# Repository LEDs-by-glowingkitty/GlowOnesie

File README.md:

# GlowOnesie
All design files and details about the cat onesies which I wear, with glowing moving ears. Great for everyday use, parties and other occasions.

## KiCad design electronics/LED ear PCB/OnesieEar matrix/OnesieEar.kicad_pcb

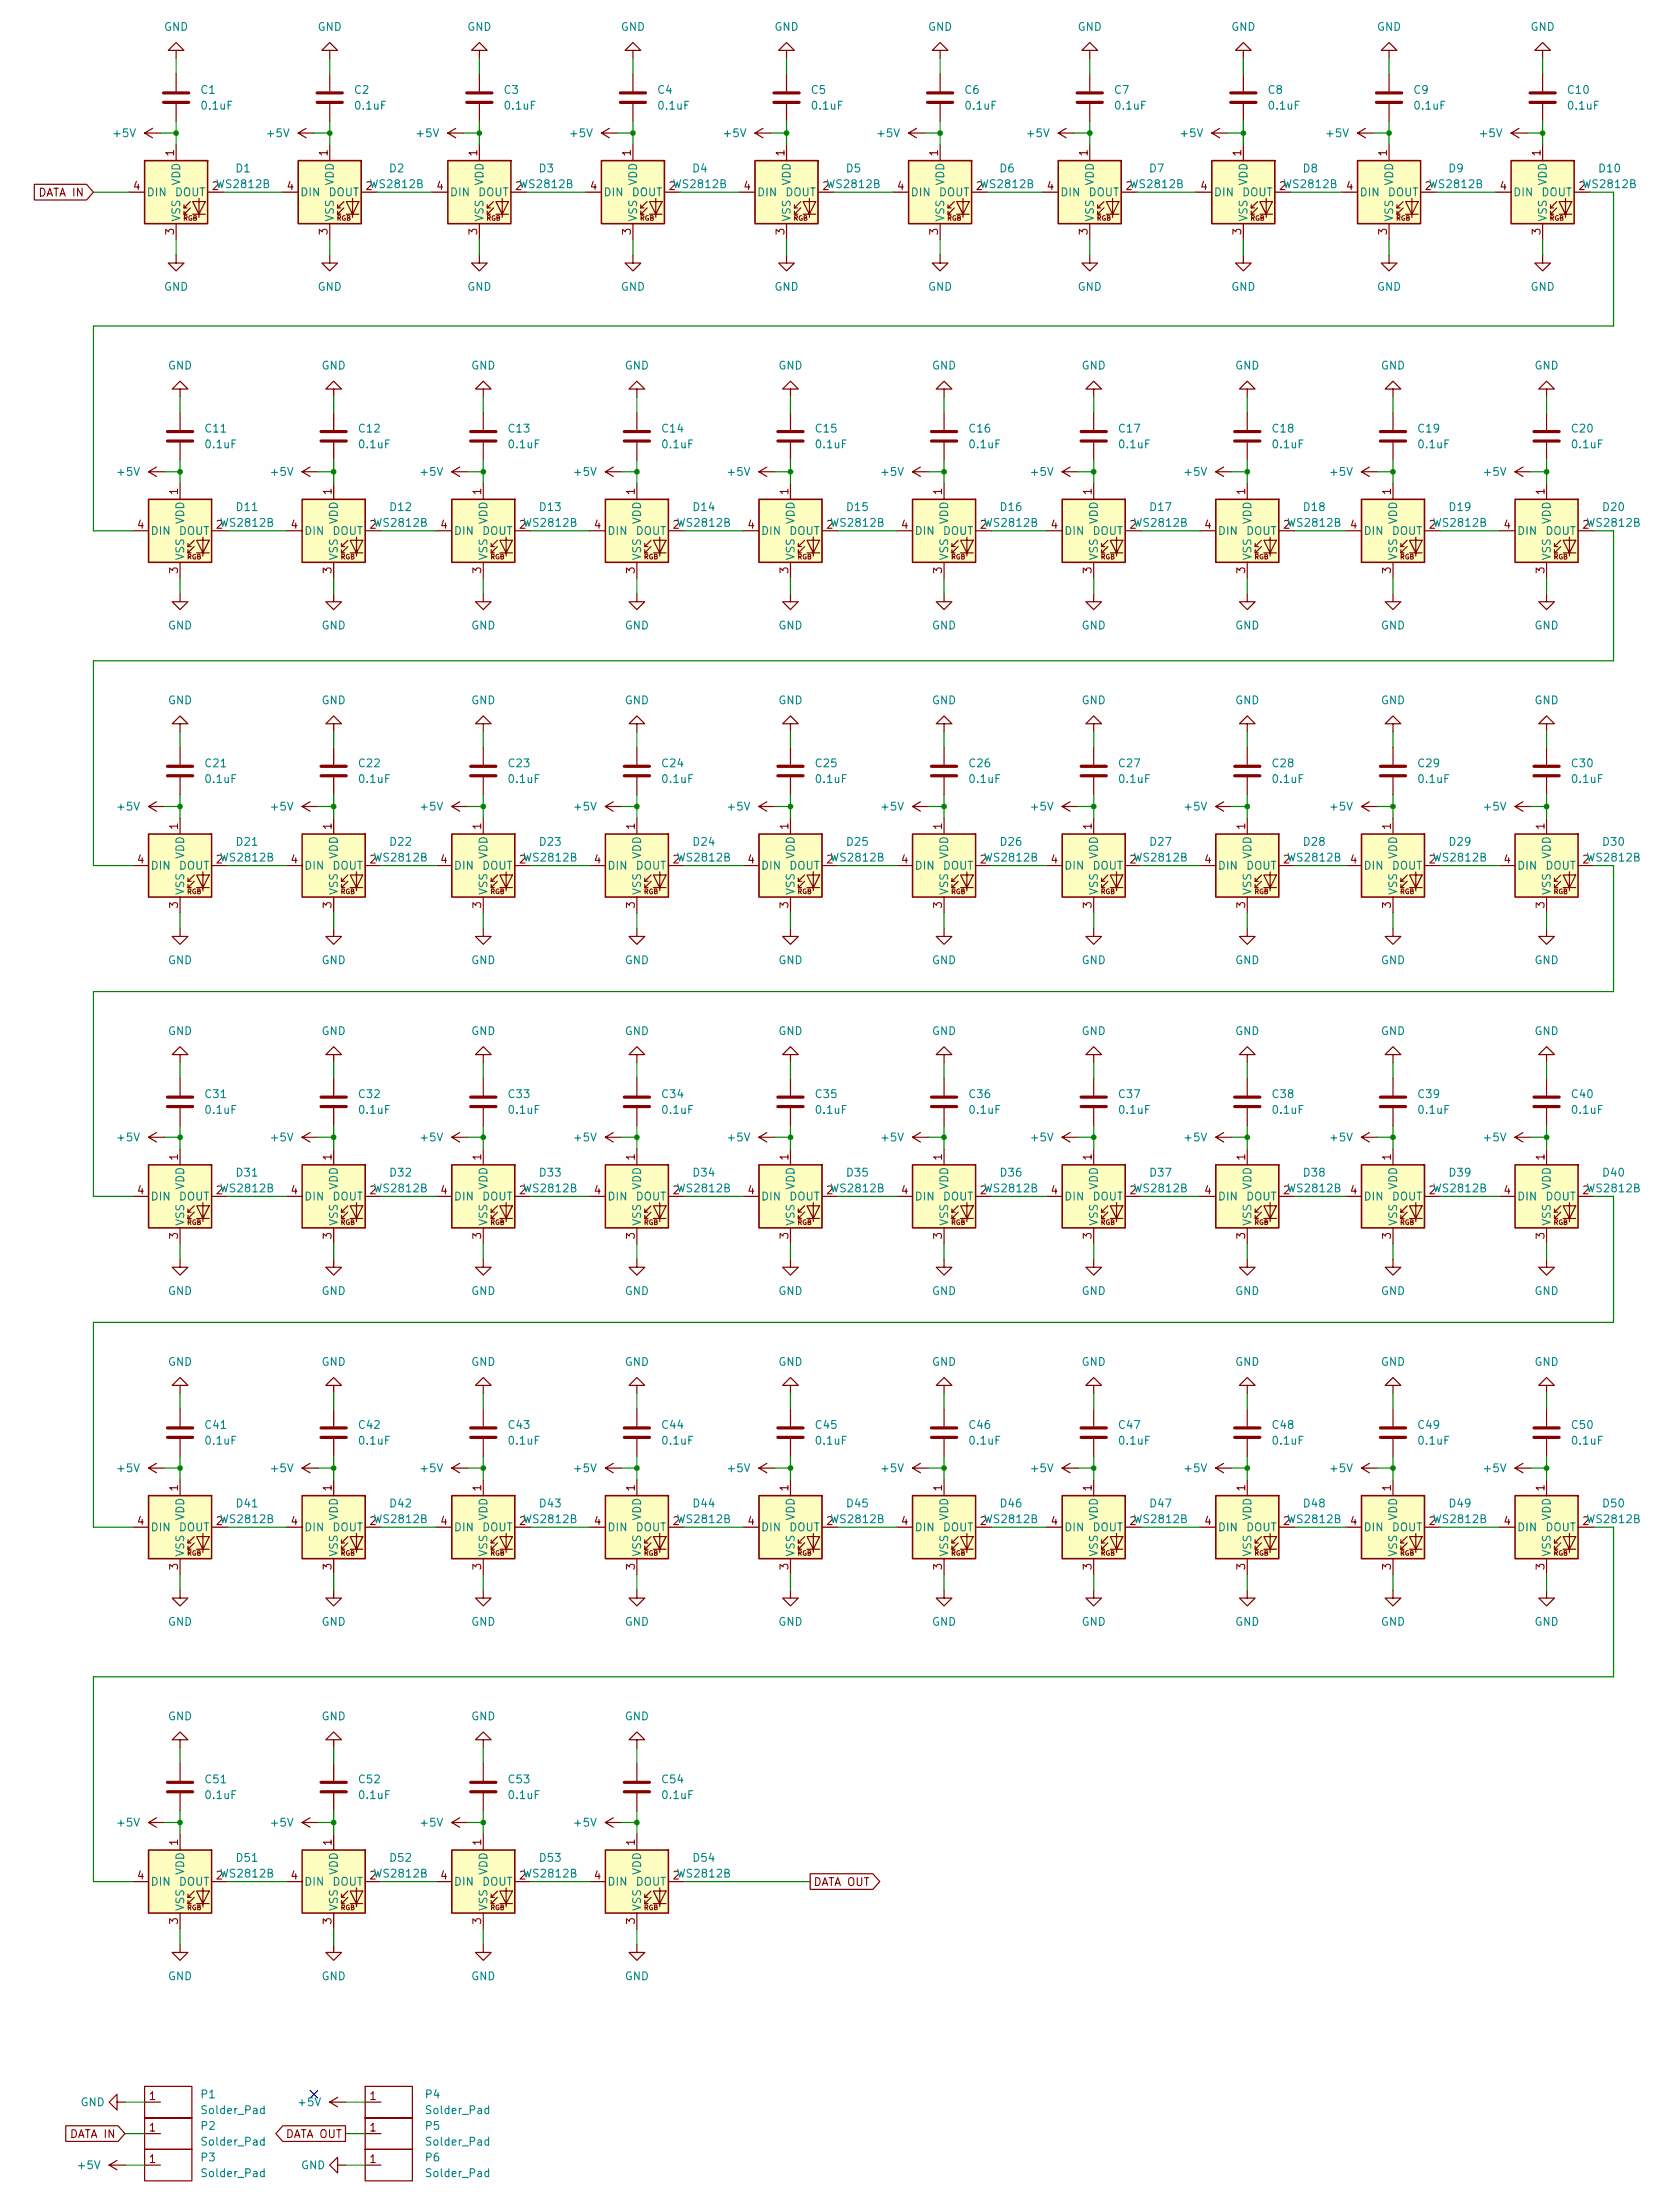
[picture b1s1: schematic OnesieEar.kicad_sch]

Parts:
C1, C2, C3, C4, C5, C6, C7, C8, C9, C10, C11, C12, C13, C14, C15, C16, C17, C18, C19, C20, C21, C22, C23, C24, C25, C26, C27, C28, C29, C30, C31, C32, C33, C34, C35, C36, C37, C38, C39, C40, C41, C42, C43, C44, C45, C46, C47, C48, C49, C50, C51, C52, C53, C54: 0.1uF; C_0603_1608Metric_Pad1.08x0.95mm_HandSolder; LCSC # C14663
D1, D2, D3, D4, D5, D6, D7, D8, D9, D10, D11, D12, D13, D14, D15, D16, D17, D18, D19, D20, D21, D22, D23, D24, D25, D26, D27, D28, D29, D30, D31, D32, D33, D34, D35, D36, D37, D38, D39, D40, D41, D42, D43, D44, D45, D46, D47, D48, D49, D50, D51, D52, D53, D54: WS2812B; LED_WS2812B_PLCC4_5.0x5.0mm_P3.2mm; LCSC # C2843785
P1, P2, P3, P4, P5, P6: Solder_Pad; Solder pad

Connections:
+5V: C1.1, C2.1, C3.1, C4.1, C5.1, C6.1, C7.1, C8.1, C9.1, C10.1, C11.1, C12.1, C13.1, C14.1, C15.1, C16.1, C17.1, C18.1, C19.1, C20.1, C21.1, C22.1, C23.1, C24.1, C25.1, C26.1, C27.1, C28.1, C29.1, C30.1, C31.1, C32.1, C33.1, C34.1, C35.1, C36.1, C37.1, C38.1, C39.1, C40.1, C41.1, C42.1, C43.1, C44.1, C45.1, C46.1, C47.1, C48.1, C49.1, C50.1, C51.1, C52.1, C53.1, C54.1, D1.1 (VDD), D2.1 (VDD), D3.1 (VDD), D4.1 (VDD), D5.1 (VDD), D6.1 (VDD), D7.1 (VDD), D8.1 (VDD), D9.1 (VDD), D10.1 (VDD), D11.1 (VDD), D12.1 (VDD), D13.1 (VDD), D14.1 (VDD), D15.1 (VDD), D16.1 (VDD), D17.1 (VDD), D18.1 (VDD), D19.1 (VDD), D20.1 (VDD), D21.1 (VDD), D22.1 (VDD), D23.1 (VDD), D24.1 (VDD), D25.1 (VDD), D26.1 (VDD), D27.1 (VDD), D28.1 (VDD), D29.1 (VDD), D30.1 (VDD), D31.1 (VDD), D32.1 (VDD), D33.1 (VDD), D34.1 (VDD), D35.1 (VDD), D36.1 (VDD), D37.1 (VDD), D38.1 (VDD), D39.1 (VDD), D40.1 (VDD), D41.1 (VDD), D42.1 (VDD), D43.1 (VDD), D44.1 (VDD), D45.1 (VDD), D46.1 (VDD), D47.1 (VDD), D48.1 (VDD), D49.1 (VDD), D50.1 (VDD), D51.1 (VDD), D52.1 (VDD), D53.1 (VDD), D54.1 (VDD), P3.1, P4.1
DATA IN: D1.4 (DIN), P2.1
DATA OUT: D54.2 (DOUT), P5.1
GND: C1.2, C2.2, C3.2, C4.2, C5.2, C6.2, C7.2, C8.2, C9.2, C10.2, C11.2, C12.2, C13.2, C14.2, C15.2, C16.2, C17.2, C18.2, C19.2, C20.2, C21.2, C22.2, C23.2, C24.2, C25.2, C26.2, C27.2, C28.2, C29.2, C30.2, C31.2, C32.2, C33.2, C34.2, C35.2, C36.2, C37.2, C38.2, C39.2, C40.2, C41.2, C42.2, C43.2, C44.2, C45.2, C46.2, C47.2, C48.2, C49.2, C50.2, C51.2, C52.2, C53.2, C54.2, D1.3 (VSS), D2.3 (VSS), D3.3 (VSS), D4.3 (VSS), D5.3 (VSS), D6.3 (VSS), D7.3 (VSS), D8.3 (VSS), D9.3 (VSS), D10.3 (VSS), D11.3 (VSS), D12.3 (VSS), D13.3 (VSS), D14.3 (VSS), D15.3 (VSS), D16.3 (VSS), D17.3 (VSS), D18.3 (VSS), D19.3 (VSS), D20.3 (VSS), D21.3 (VSS), D22.3 (VSS), D23.3 (VSS), D24.3 (VSS), D25.3 (VSS), D26.3 (VSS), D27.3 (VSS), D28.3 (VSS), D29.3 (VSS), D30.3 (VSS), D31.3 (VSS), D32.3 (VSS), D33.3 (VSS), D34.3 (VSS), D35.3 (VSS), D36.3 (VSS), D37.3 (VSS), D38.3 (VSS), D39.3 (VSS), D40.3 (VSS), D41.3 (VSS), D42.3 (VSS), D43.3 (VSS), D44.3 (VSS), D45.3 (VSS), D46.3 (VSS), D47.3 (VSS), D48.3 (VSS), D49.3 (VSS), D50.3 (VSS), D51.3 (VSS), D52.3 (VSS), D53.3 (VSS), D54.3 (VSS), P1.1, P6.1
unnamed: D1.2 (DOUT), D2.4 (DIN)
unnamed: D2.2 (DOUT), D3.4 (DIN)
unnamed: D3.2 (DOUT), D4.4 (DIN)
unnamed: D4.2 (DOUT), D5.4 (DIN)
unnamed: D5.2 (DOUT), D6.4 (DIN)
unnamed: D6.2 (DOUT), D7.4 (DIN)
unnamed: D7.2 (DOUT), D8.4 (DIN)
unnamed: D8.2 (DOUT), D9.4 (DIN)
unnamed: D9.2 (DOUT), D10.4 (DIN)
unnamed: D10.2 (DOUT), D11.4 (DIN)
unnamed: D11.2 (DOUT), D12.4 (DIN)
unnamed: D12.2 (DOUT), D13.4 (DIN)
unnamed: D13.2 (DOUT), D14.4 (DIN)
unnamed: D14.2 (DOUT), D15.4 (DIN)
unnamed: D15.2 (DOUT), D16.4 (DIN)
unnamed: D16.2 (DOUT), D17.4 (DIN)
unnamed: D17.2 (DOUT), D18.4 (DIN)
unnamed: D18.2 (DOUT), D19.4 (DIN)
unnamed: D19.2 (DOUT), D20.4 (DIN)
unnamed: D20.2 (DOUT), D21.4 (DIN)
unnamed: D21.2 (DOUT), D22.4 (DIN)
unnamed: D22.2 (DOUT), D23.4 (DIN)
unnamed: D23.2 (DOUT), D24.4 (DIN)
unnamed: D24.2 (DOUT), D25.4 (DIN)
unnamed: D25.2 (DOUT), D26.4 (DIN)
unnamed: D26.2 (DOUT), D27.4 (DIN)
unnamed: D27.2 (DOUT), D28.4 (DIN)
unnamed: D28.2 (DOUT), D29.4 (DIN)
unnamed: D29.2 (DOUT), D30.4 (DIN)
unnamed: D30.2 (DOUT), D31.4 (DIN)
unnamed: D31.2 (DOUT), D32.4 (DIN)
unnamed: D32.2 (DOUT), D33.4 (DIN)
unnamed: D33.2 (DOUT), D34.4 (DIN)
unnamed: D34.2 (DOUT), D35.4 (DIN)
unnamed: D35.2 (DOUT), D36.4 (DIN)
unnamed: D36.2 (DOUT), D37.4 (DIN)
unnamed: D37.2 (DOUT), D38.4 (DIN)
unnamed: D38.2 (DOUT), D39.4 (DIN)
unnamed: D39.2 (DOUT), D40.4 (DIN)
unnamed: D40.2 (DOUT), D41.4 (DIN)
unnamed: D41.2 (DOUT), D42.4 (DIN)
unnamed: D42.2 (DOUT), D43.4 (DIN)
unnamed: D43.2 (DOUT), D44.4 (DIN)
unnamed: D44.2 (DOUT), D45.4 (DIN)
unnamed: D45.2 (DOUT), D46.4 (DIN)
unnamed: D46.2 (DOUT), D47.4 (DIN)
unnamed: D47.2 (DOUT), D48.4 (DIN)
unnamed: D48.2 (DOUT), D49.4 (DIN)
unnamed: D49.2 (DOUT), D50.4 (DIN)
unnamed: D50.2 (DOUT), D51.4 (DIN)
unnamed: D51.2 (DOUT), D52.4 (DIN)
unnamed: D52.2 (DOUT), D53.4 (DIN)
unnamed: D53.2 (DOUT), D54.4 (DIN)

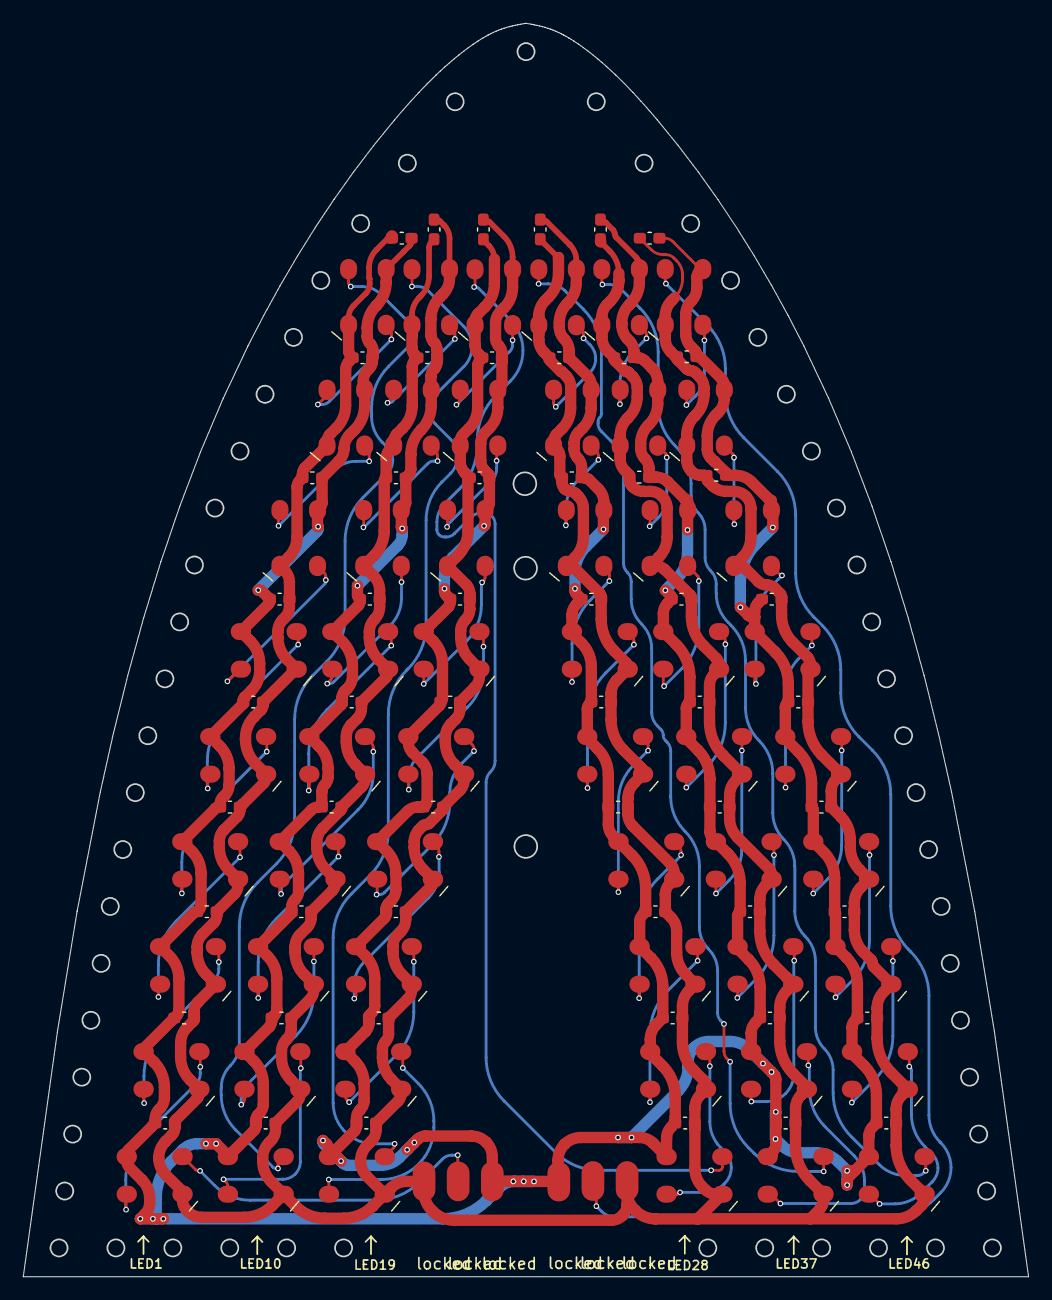
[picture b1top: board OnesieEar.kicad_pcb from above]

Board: 2 copper layers, 88.3 x 110.1 mm, 114 parts (0 on the bottom side), 57 nets.

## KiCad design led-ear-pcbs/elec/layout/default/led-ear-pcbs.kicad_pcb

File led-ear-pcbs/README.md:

# led-ear-pcbs

Wooohooo a new package!

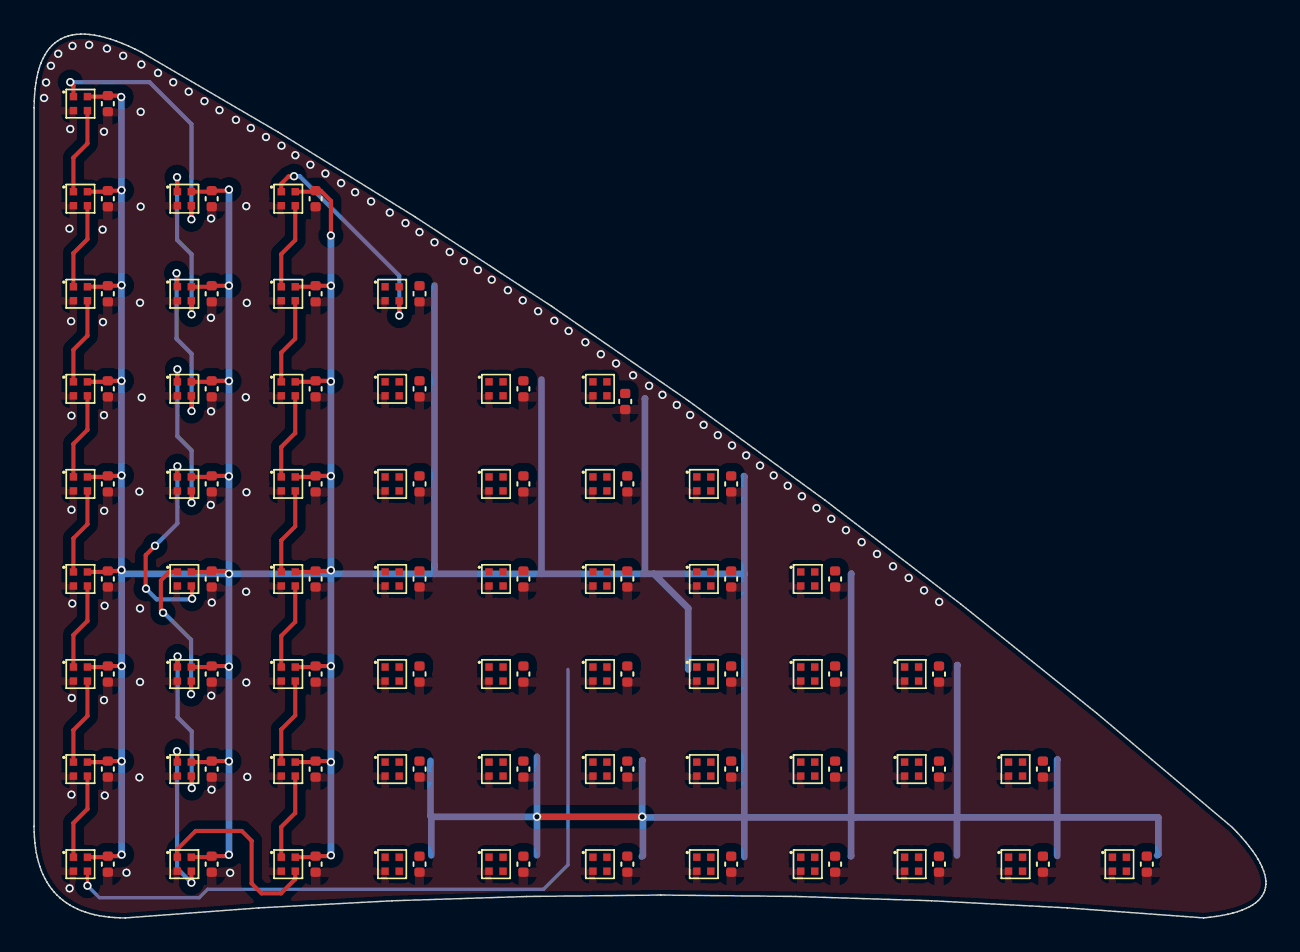
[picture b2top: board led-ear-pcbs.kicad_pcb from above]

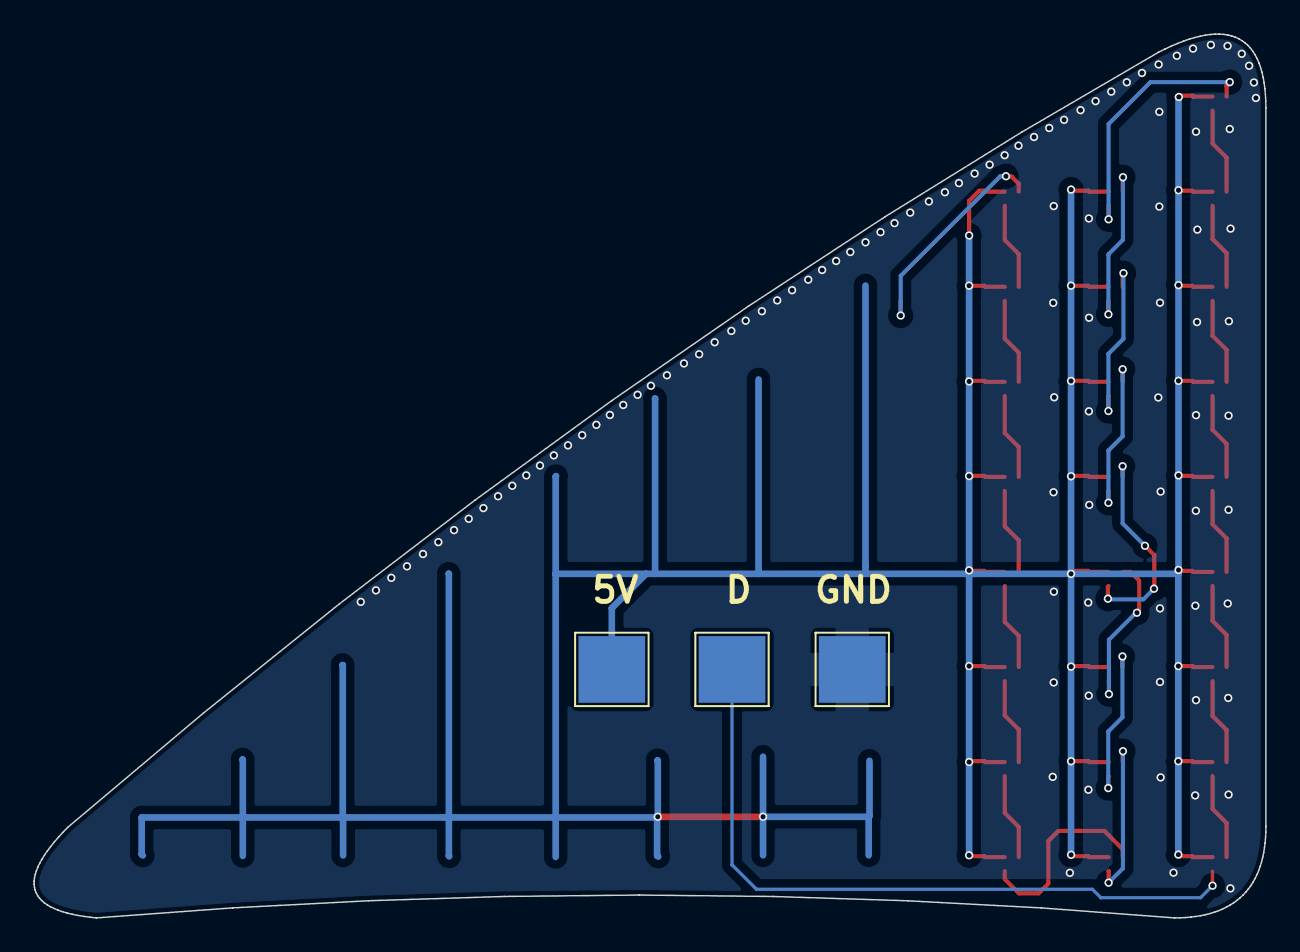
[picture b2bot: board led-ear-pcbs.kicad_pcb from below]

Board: 2 copper layers, 73.8 x 53.0 mm, 121 parts (3 on the bottom side), 61 nets.

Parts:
C1, C2, C3, C4, C5, C6, C7, C8, C9, C10, C11, C12, C13, C14, C15, C16, C17, C18, C19, C20, C21, C22, C23, C24, C25, C26, C27, C28, C29, C30, C31, C32, C33, C34, C35, C36, C37, C38, C39, C40, C41, C42, C43, C44, C45, C46, C47, C48, C49, C50, C51, C52, C53, C54, C55, C56, C57, C58, C59: 16V 100nF X7R ±10% 0402 Multilayer Ceramic Capaci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; C0402
U1, U2, U3: TestPoint_Pad_4.0x4.0mm
U4, U5, U6, U7, U8, U9, U10, U11, U12, U13, U14, U15, U16, U17, U18, U19, U20, U21, U22, U23, U24, U25, U26, U27, U28, U29, U30, U31, U32, U33, U34, U35, U36, U37, U38, U39, U40, U41, U42, U43, U44, U45, U46, U47, U48, U49, U50, U51, U52, U53, U54, U55, U56, U57, U58, U59, U60, U61, U62: LED-SMD_4P-L1.0-W1.0-TL_XL-1010RGBC-WS2812B

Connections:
din: U2.1, U4.4
gnd: C1.2, C2.2, C3.2, C4.2, C5.2, C6.2, C7.2, C8.2, C9.2, C10.2, C11.2, C12.2, C13.2, C14.2, C15.2, C16.2, C17.2, C18.2, C19.2, C20.2, C21.2, C22.2, C23.2, C24.2, C25.2, C26.2, C27.2, C28.2, C29.2, C30.2, C31.2, C32.2, C33.2, C34.2, C35.2, C36.2, C37.2, C38.2, C39.2, C40.2, C41.2, C42.2, C43.2, C44.2, C45.2, C46.2, C47.2, C48.2, C49.2, C50.2, C51.2, C52.2, C53.2, C54.2, C55.2, C56.2, C57.2, C58.2, C59.2, U3.1, U4.3, U5.3, U6.3, U7.3, U8.3, U9.3, U10.3, U11.3, U12.3, U13.3, U14.3, U15.3, U16.3, U17.3, U18.3, U19.3, U20.3, U21.3, U22.3, U23.3, U24.3, U25.3, U26.3, U27.3, U28.3, U29.3, U30.3, U31.3, U32.3, U33.3, U34.3, U35.3, U36.3, U37.3, U38.3, U39.3, U40.3, U41.3, U42.3, U43.3, U44.3, U45.3, U46.3, U47.3, U48.3, U49.3, U50.3, U51.3, U52.3, U53.3, U54.3, U55.3, U56.3, U57.3, U58.3, U59.3, U60.3, U61.3, U62.3
led_1-dout: U4.1, U5.4
led_2-dout: U5.1, U6.4
led_3-dout: U6.1, U7.4
led_4-dout: U7.1, U8.4
led_5-dout: U8.1, U9.4
led_6-dout: U9.1, U10.4
led_7-dout: U10.1, U11.4
led_8-dout: U11.1, U12.4
led_9-dout: U12.1, U13.4
led_10-dout: U13.1, U14.4
led_11-dout: U14.1, U15.4
led_12-dout: U15.1, U16.4
led_13-dout: U16.1, U17.4
led_14-dout: U17.1, U18.4
led_15-dout: U18.1, U19.4
led_16-dout: U19.1, U20.4
led_17-dout: U20.1, U21.4
led_18-dout: U21.1, U22.4
led_19-dout: U22.1, U23.4
led_20-dout: U23.1, U24.4
led_21-dout: U24.1, U25.4
led_22-dout: U25.1, U26.4
led_23-dout: U26.1, U27.4
led_24-dout: U27.1, U28.4
led_25-dout: U28.1, U29.4
led_26-dout: U29.1, U30.4
led_27-dout: U30.1, U31.4
led_28-dout: U31.1, U32.4
led_29-dout: U32.1, U33.4
led_30-dout: U33.1, U34.4
led_31-dout: U34.1, U35.4
led_32-dout: U35.1, U36.4
led_33-dout: U36.1, U37.4
led_34-dout: U37.1, U38.4
led_35-dout: U38.1, U39.4
led_36-dout: U39.1, U40.4
led_37-dout: U40.1, U41.4
led_38-dout: U41.1, U42.4
led_39-dout: U42.1, U43.4
led_40-dout: U43.1, U44.4
led_41-dout: U44.1, U45.4
led_42-dout: U45.1, U46.4
led_43-dout: U46.1, U47.4
led_44-dout: U47.1, U48.4
led_45-dout: U48.1, U49.4
led_46-dout: U49.1, U50.4
led_47-dout: U50.1, U51.4
led_48-dout: U51.1, U52.4
led_49-dout: U52.1, U53.4
led_50-dout: U53.1, U54.4
led_51-dout: U54.1, U55.4
led_52-dout: U55.1, U56.4
led_53-dout: U56.1, U57.4
led_54-dout: U57.1, U58.4
led_55-dout: U58.1, U59.4
led_56-dout: U59.1, U60.4
led_57-dout: U60.1, U61.4
led_58-dout: U61.1, U62.4
vcc: C1.1, C2.1, C3.1, C4.1, C5.1, C6.1, C7.1, C8.1, C9.1, C10.1, C11.1, C12.1, C13.1, C14.1, C15.1, C16.1, C17.1, C18.1, C19.1, C20.1, C21.1, C22.1, C23.1, C24.1, C25.1, C26.1, C27.1, C28.1, C29.1, C30.1, C31.1, C32.1, C33.1, C34.1, C35.1, C36.1, C37.1, C38.1, C39.1, C40.1, C41.1, C42.1, C43.1, C44.1, C45.1, C46.1, C47.1, C48.1, C49.1, C50.1, C51.1, C52.1, C53.1, C54.1, C55.1, C56.1, C57.1, C58.1, C59.1, U1.1, U4.2, U5.2, U6.2, U7.2, U8.2, U9.2, U10.2, U11.2, U12.2, U13.2, U14.2, U15.2, U16.2, U17.2, U18.2, U19.2, U20.2, U21.2, U22.2, U23.2, U24.2, U25.2, U26.2, U27.2, U28.2, U29.2, U30.2, U31.2, U32.2, U33.2, U34.2, U35.2, U36.2, U37.2, U38.2, U39.2, U40.2, U41.2, U42.2, U43.2, U44.2, U45.2, U46.2, U47.2, U48.2, U49.2, U50.2, U51.2, U52.2, U53.2, U54.2, U55.2, U56.2, U57.2, U58.2, U59.2, U60.2, U61.2, U62.2

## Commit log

2023-09-19 add files and descriptions for onesies (in progress)
2023-09-20 added cutting patterns for party onesie
2023-09-20 add missing part
2023-09-20 fixed
2023-09-20 added thinn and long edition patterns
2023-09-21 added zipper details for party onesie
2023-09-21 updated onesie names and description
2023-09-21 description update
2023-09-23 updated pdfs
2023-09-23 added single patterns as svg
2023-09-24 added sparkly pattern
2023-09-24 added svg
2023-09-24 updated pattern
2023-09-24 updated patterns
2023-09-24 update patterns
2024-07-07 started recreating led ear pcb
2024-07-07 added leds
2024-07-10 added all components and specs, starting placing components
2024-07-10 made progress with routing pcb
2024-07-20 updated atopile, tried to fix crash
